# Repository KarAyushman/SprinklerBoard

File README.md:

# SprinklerBoard
This Project is a Cumulation of a NodeMCU board incorporated into a circuit to control and manage the Sprinkler Sytems at my residence involving Temperature and Humidity Sensors as extra features and an Android App encoded in Java to control the same. ThingSpeak is being used as the BackEnd API to communicate with the App and the Development Board both ways. Elaborate Documentation will be added later.

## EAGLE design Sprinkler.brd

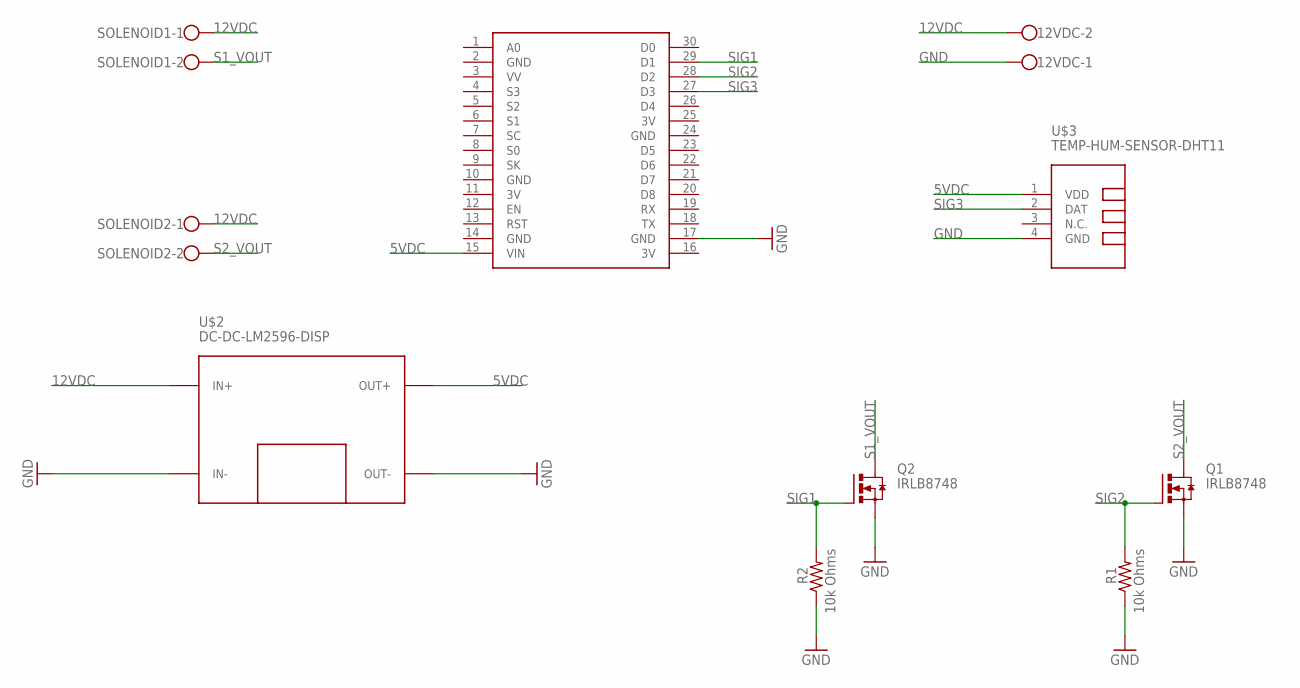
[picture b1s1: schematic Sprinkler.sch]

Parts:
12VDC: W237-102
Q1, Q2: IRLB8748; TO220AH
R1, R2: 10k Ohms; 0204/7
SOLENOID1, SOLENOID2: W237-102
U$1: NODEMCU
U$2: DC-DC-LM2596-DISP
U$3: TEMP-HUM-SENSOR-DHT11

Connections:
3V: U$1.11 (3V), U$1.16 (3V), U$1.25 (3V)
5VDC: U$1.15 (VIN), U$2.OUT+, U$3.1 (VDD)
12VDC: 12VDC.2, SOLENOID1.1, SOLENOID2.1, U$2.IN+
GND: 12VDC.1, Q1.E (S), Q2.E (S), R1.1, R2.1, U$1.2 (GND), U$1.10 (GND), U$1.14 (GND), U$1.17 (GND), U$1.24 (GND), U$2.IN-, U$2.OUT-, U$3.4 (GND)
S1_VOUT: Q2.C (D), SOLENOID1.2
S2_VOUT: Q1.C (D), SOLENOID2.2
SIG1: Q2.B (G), R2.2, U$1.29 (D1)
SIG2: Q1.B (G), R1.2, U$1.28 (D2)
SIG3: U$1.27 (D3), U$3.2 (DAT)

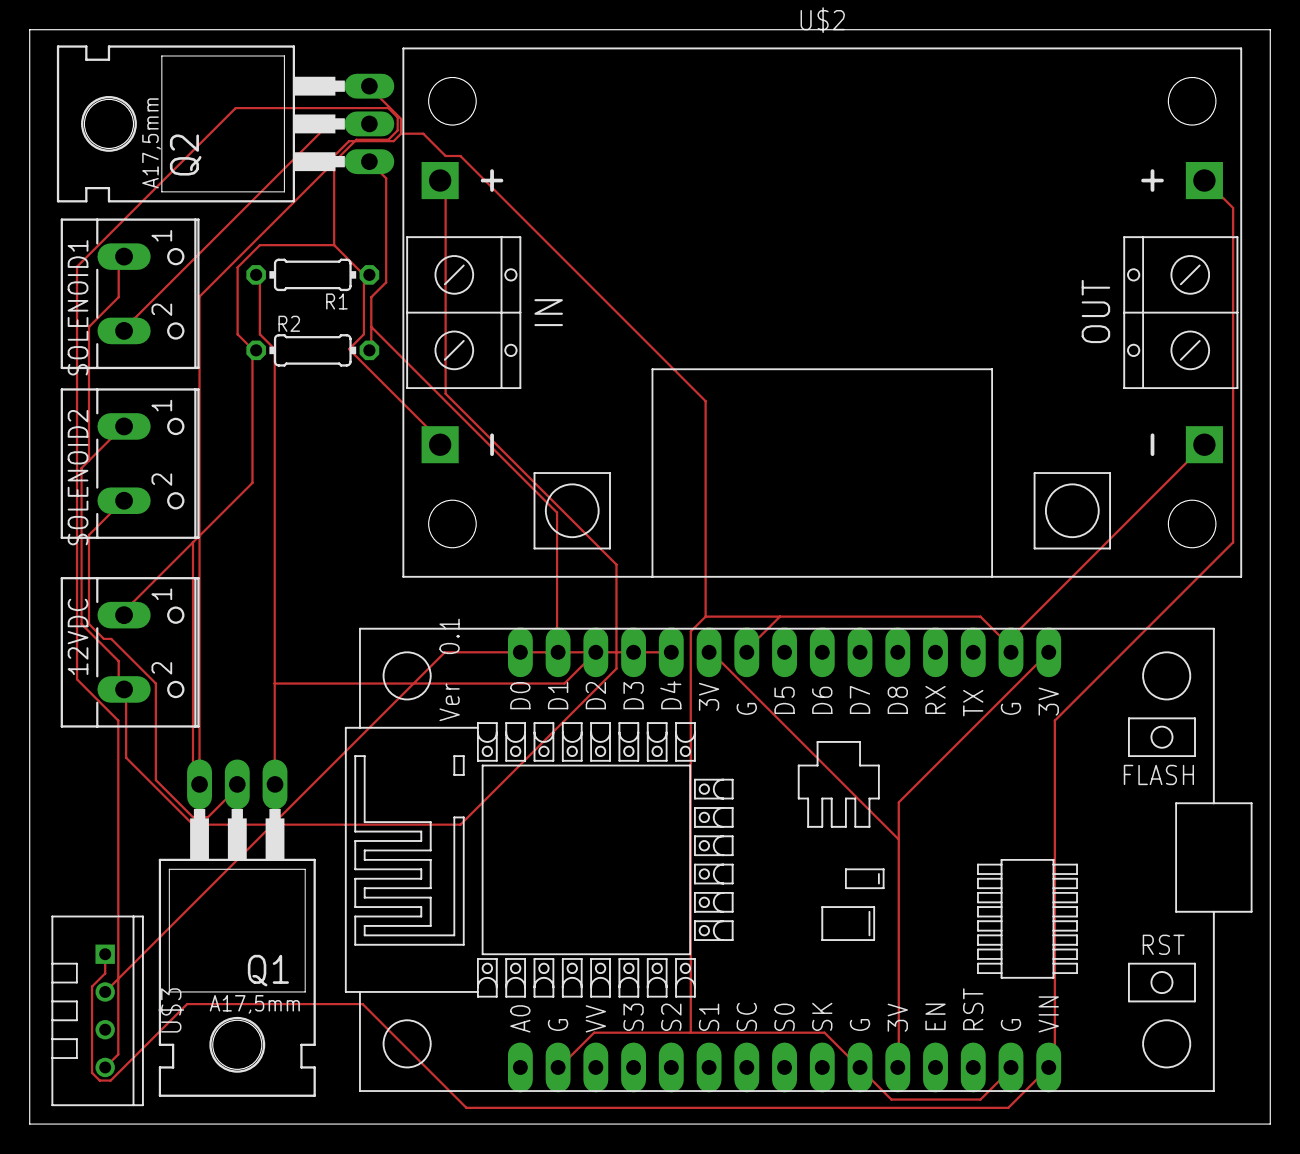
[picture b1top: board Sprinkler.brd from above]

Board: 2 copper layers, 83.5 x 73.7 mm, 10 parts (0 on the bottom side), 9 nets.

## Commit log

2021-11-09 Changes to Directory Structure

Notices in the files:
parts and their libraries:
diy-modules: Released under the Creative Commons Attribution 4.0 International License: http://creativecommons.org/licenses/by/4.0
